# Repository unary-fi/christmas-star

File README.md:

# Christmas Star

A decorative smart LED Christmas star: 132 RGB LEDs on two faces, Bluetooth,
an accelerometer and a 2 Gbit flash for animations. This repository holds the
hardware design (KiCad), the Zephyr firmware, the Android app and the PC tools.

Releases (firmware images and the Android app) are published in
[unary-fi/christmas-star-releases](https://github.com/unary-fi/christmas-star-releases/releases).

# Hardware

The ChristmasStar 1.0 hardware comprises the following components:
- STM32F030RCT6 ARM Cortex-M0 MCU (256 KB flash, 32 KB RAM)
- 8.0 MHz oscillator
- BM78SPPS5MC2 BlueTooth serial port module
- LSM6DS3 iNEMO 6-axis MEMS inertial module
- ZD35Q2GC-IB NAND Flash memory, 2 Gb
- 132 digital RGB LEDs in one chain, 66 LEDs per side

See [docs/led-layout.md](docs/led-layout.md) for how the LEDs are arranged and
[docs/hw-schematic-review.md](docs/hw-schematic-review.md) for known hardware issues.

# Software

The firmware in [sw/](sw/) is a [Zephyr](https://zephyrproject.org) application
with its own board definition (`christmas_star`). The Android app in
[android/](android/) controls the star over Bluetooth LE.

## Features

- Real-time LED effects at 50 fps. The LED data is sent by SPI2 (transmit-only)
  with DMA from the app's own driver, so it is unaffected by interrupts.
- Christmas effects that run on the star itself: Golden Star, Liquid Gold
  (flows as the star is tilted), Snowfall, Shooting Stars, Candlelight,
  Hearth & Frost (different faces that trade places), Northern Lights, Candy
  Cane, Tree Lights, Star of Bethlehem, Fireworks, Christmas Disco, Frost, Twinkle, Comets and
  Rainbow, with an adjustable speed.
- The app and Star Studio get the effect list and animated previews from the
  star (`app effects`, `app preview`), so new effects arrive with a firmware
  update alone. Previews are cached per firmware version.
- Shake to drop: shaking knocks lights loose in their current colours, on top
  of any effect, picture or video (`shake on|off`).
- **Comet**, a game played on the star and steered from the app (see
  *Comet, the game*).
- Command line over Bluetooth (BM78), including direct LED control and a
  binary live-stream mode used by the app for photos and videos.
- One effect at a time in the 2 Gbit NAND (about 655 000 frames, 3.6 h at
  50 fps), uploaded over Bluetooth with XMODEM-1K.
- The star resumes what it was showing after a restart (effect, manual or
  picture frame, speed, shake on/off).
- Missing LEDs: if an LED is bridged on the board, or is faulty and only
  passes the data through, mark it missing and the firmware skips it in the
  chain. The default list is empty (`CONFIG_STAR_DEFAULT_MISSING_LEDS`); the
  first prototype has D259 bridged (`led missing add D259`).
- Supply protection: the firmware measures the 3V3 rail every frame and
  lowers the LED current limit when it sags, so the Bluetooth module (3.3 V
  minimum) keeps running. The default limit is 600 mA (`led limit`);
  `led status` shows the rail voltage and the learnt limit.
- Pairing: each star belongs to one phone (or PC). Its Bluetooth command line
  stays locked until the app proves the owner's key, so several stars and
  phones can share a room. A developer key opens every star (see *Pairing*).
- Names: stars can be renamed from the app or Star Studio; the name is what
  phones and PCs see when they search.
- Settings (missing LEDs, brightness, current limit, IMU axes) and the
  running state are stored in the MCU's internal flash.

## Setting up (Windows)

1. Install Python 3.12, CMake, Ninja and the SEGGER J-Link software.
2. Create the Python environment and the west workspace (the repository root
   is the workspace, `sw/` is the manifest):

   ```powershell
   py -3.12 -m venv .venv
   .venv\Scripts\pip install west pyserial xmodem pillow pylink-square pytest bleak cryptography intelhex click cbor2
   .venv\Scripts\west init -l sw
   .venv\Scripts\west update
   .venv\Scripts\pip install -r zephyr\scripts\requirements-base.txt
   ```

3. Install the [Zephyr SDK](https://github.com/zephyrproject-rtos/sdk-ng/releases)
   1.0.1 minimal bundle with the `arm-zephyr-eabi` toolchain into
   `%USERPROFILE%\zephyr-sdk-1.0.1`.
4. In each new PowerShell session: `. .\sw\tools\env.ps1`
5. Developer key (optional, for your own builds only): put 32 random hex
   digits in `sw/dev_key.txt` (ignored by git), e.g.
   `python -c "import secrets; open('sw/dev_key.txt','w').write(secrets.token_hex(16))"`.
   Firmware built with it accepts this key on every star; `star_ble.py` reads
   it from the same file, and Star Studio takes it on its *Developer* page.
   Keep it private, and never
   publish firmware built with it: anyone could read the key out of the image.
   Published releases are built without one (CI has no key; locally,
   `$env:STAR_NO_DEV_KEY = "1"` before a pristine build leaves it out).

## Building and flashing

```powershell
west build --sysbuild -b christmas_star sw -d build/star            # release
west build --sysbuild -b christmas_star sw -d build/debug -- -DEXTRA_CONF_FILE=debug.conf
west flash -d build/star                                 # J-Link on J401
```

Each build contains the MCUboot bootloader and the firmware, signed with
`sw/signing_key.pem` (ECDSA P-256, ignored by git). Stars only start firmware
signed with the key their bootloader was built with. Official releases are
signed with the project's key, which is not public; for your own builds,
create a key of your own and install your bootloader once with a J-Link:

```powershell
python bootloader\mcuboot\scripts\imgtool.py keygen -k sw\signing_key.pem -t ecdsa-p256
```

Flash layout (256 KB): MCUboot 32 KB, the running firmware 108 KB, the slot
for an update 108 KB, settings 8 KB (at the same place as before the
bootloader, so the stored settings survive). The version comes from
[sw/VERSION](sw/VERSION).

### Firmware update over Bluetooth

```powershell
python sw\tools\update_firmware.py build\star\sw\zephyr\zephyr.signed.bin
python sw\tools\update_firmware.py --star "Living room" build\star\sw\zephyr\zephyr.signed.bin
```

or the *Firmware* card in Star Studio (several stars, one after the other).
The image goes into the second slot with XMODEM-1K (about 35 s from a PC);
`fw apply` restarts the star and MCUboot checks the signature and swaps the
slots. The new firmware confirms itself after 20 s; if it crashes or hangs
before that, the next restart brings the old one back. On the command line:
`fw status`, `fw upload`, `fw apply [permanent]`, `fw confirm`.

Updates need the BOOT0 pull-down: without it, the restart ends in ST's ROM
bootloader. Boards are switched to the bootloader layout once with the
J-Link (`west flash`); after that, Bluetooth is enough.

The debug build adds a second shell over SEGGER RTT, so the star can be
controlled through the J-Link without Bluetooth:

```powershell
python sw\tools\rtt_shell.py --boot-flash "led status" "nand info" "imu read"
```

The debug build can also reach the BM78 through the J-Link: `bt bridge test`
restarts the module in test mode and relays its UART over RTT.
`python sw\tools\bm78_bridge.py probe|dump|hci|com|rename|restore` uses this
to read the module's version and configuration EEPROM, rename the module,
write a backup back (keep backups private: they contain the module's address and
pairing keys), or connect Microchip's
configuration tool through a virtual null-modem pair (com0com).

> **BOOT0 on hardware 1.0:** BOOT0 has no pull-down, and on the prototype
> every reset starts ST's ROM bootloader instead of the firmware. Connecting
> the J-Link also resets the MCU. Until the board gets a 10 kΩ pull-down,
> start the firmware with `rtt_shell.py --boot-flash`, which maps flash to
> address 0 and starts MCUboot, which starts the firmware.

## Tests

```powershell
west build -p always -b qemu_cortex_m3 sw/tests/unit -d build/tests -t run
python -m pytest sw/tools/tests pc/tests
```

## Command line

The star's Bluetooth module appears under its name (**"Dual-SPP"** until it is
first renamed; after renaming it is also found by its service, whatever the
name). Windows 11's
*Add device* dialog may not list it; pair it with the classic wizard instead
(run `DevicePairingWizard.exe`). Windows pairs it as a Bluetooth LE device,
which creates no COM port, so use the BLE terminal:

```powershell
python sw\tools\star_ble.py --list             # nearby stars
python sw\tools\star_ble.py                    # interactive terminal (nearest star)
python sw\tools\star_ble.py --star "Living room" "led status"
python sw\tools\star_ble.py --pair             # pair the star with this PC
```

The tool logs in with the developer key, or with this PC's own key
(`~/.christmas-star/pc_key`) for a star paired with the PC.

Phones can use any BLE terminal app that supports the Microchip Transparent
UART service. On a system where the star pairs as a Classic SPP device, open
its COM port at 115200 baud instead. Type `help` for all commands.

| Command | Description |
|---|---|
| `set_led <side> <index> <color>` | Set one LED. Side 0 = both, 1 = front (D2xx), 2 = back (D3xx); index 1–66 is the designator number; colour `0xRRGGBB`, `#RRGGBB` or `RRGGBB`. Example: `set_led 1 32 0xffee33` sets D232. |
| `set_all <side> <color>` | Set all LEDs of a side, e.g. `set_all 1 0xffee33`. |
| `effect list` | Effects, and the one stored in the flash. |
| `effect play <name\|flash>` | Start an effect (`flash` = the stored one). |
| `effect color <color>` | Solid colour. |
| `effect speed [25-400]` | Effect speed in percent. |
| `effect upload` | Receive a `.csfx` file with XMODEM-1K (replaces the stored effect). |
| `effect info`, `effect delete` | Stored effect details, delete it. |
| `shake [on\|off]` | Shake to drop lights, for every effect. |
| `app hello`, `app state`, `stream` | Used by the Android app (state line, binary live frames). |
| `app effects`, `app preview <id> [frames] [step_ms]` | The effects to offer (`fx <id> <flags> <title>\|<subtitle>`), and a preview clip rendered on the star. |
| `app game [start single\|double \| l \| r \| f \| pause \| resume \| stop]` | Comet, the game: start, steer (left, right, flip), pause, leave. Without arguments one `game state=... score=... best1=... best2=...` line. |
| `led missing list\|add\|del\|clear` | LEDs bridged on the board, e.g. `led missing add D259`. |
| `led test <led\|all>` | Light one LED (e.g. `D232` or logical index 0–131) or walk the chain. |
| `led brightness [0-255]`, `led limit [mA]` | Global brightness, total current limit. |
| `led map [1\|2]`, `led status` | Print the LED bitmap; frame rate and current. |
| `imu read [n]`, `imu axis [+x+y+z]`, `imu threshold [mg]` | Accelerometer values, axis mapping, shake sensitivity. |
| `bt status`, `bt reset` | Bluetooth module status pins, reset. |
| `star name [text\|--default]` | Show or set the star's name (1–16 characters, what phones see). Bluetooth restarts for a few seconds. |
| `star unpair [force]` | Release the star from its owner (`force` with developer access). |
| `star pairing [open\|reset]` | Pairing status; open the window or forget the owner (developer or J-Link). |
| `app hello`, `app auth <hmac>`, `app pair <key>` | Unlock the Bluetooth command line (see *Pairing*). |
| `nand info`, `nand test <block>` | Flash ID and geometry, read/write test. |
| `reboot` | Restart. |

## Pairing

Every star has at most one owner: a phone (the app) or a PC. Until a client
proves a key, the star's Bluetooth command line only answers `app hello`,
`app auth` and `app pair`, and it locks again whenever the link drops. The
J-Link (RTT) command line is never locked.

- `app hello` gives a fresh random nonce; the client answers
  `app auth <HMAC-SHA256(key, "auth" + nonce)>` with the owner's key or the
  developer key. The key itself never goes over the air.
- A star without an owner (new, or released by its owner) accepts a new owner
  during the first **60 s after it is plugged in**. An owned star does not.
- **Shaking the star for 5 seconds** opens pairing in any case: the star
  breathes gold for 60 s, and the next phone that taps it in the app becomes
  its owner (green flash). Releasing shows a red flash.
- The owner can release the star in the app (*Stars* → *Release this star*).
- Developer mode in the app: tap the title "Christmas Star" seven times and
  enter the developer key; *Stars* then switches freely between all stars.
  Star Studio uses the developer key saved on its *Developer* page.

The BM78 accepts one connection at a time, so a star connected to Star Studio
is not available to a phone until the studio disconnects it.

## Comet, the game

A comet runs along the star's lights. Catch the golden sparks to grow (and
the red ornaments for five points); don't run into your own tail. Every five
sparks the comet speeds up; at 40 segments the star is full and you win.

- **The track**: on each face the outline and the inner circle (the 12 LEDs
  around the centre), joined by six passages: the single LEDs between them,
  each leading from an inner corner of the outline to the circle.
- **Steering**: the comet follows its line. Tap *Left* or *Right* and it turns
  that way at the next place where it can, if that turn exists there;
  otherwise the tap is forgotten. At the end of a passage the comet turns to
  the side you tapped last (before your first tap, it keeps its direction of
  travel). A faint white light shows the next place to turn; it turns blue
  when your tap will take it. Left and right are as you see them on the face
  the comet is on.
- **One side**: the game stays on the front and is mirrored to the back, so
  everyone around the star sees the same game.
- **Both sides**: *Flip* sends the comet through the star; it carries on in
  the same direction on the other face. Sparks appear on either face, so walk
  around the star to find them, and mind your tail when you flip onto it.
  Sparks count double. A faint glow on the far face shows where the comet is.
- The app and Star Studio have a *Play* page (firmware 1.6 or later). In Star
  Studio, steer with the arrow keys (or A/D, W/S to flip), Space pauses and
  Esc leaves; every selected star plays. Leaving the app or losing the
  Bluetooth link pauses the game; after a minute in pause or game over the
  star goes back to the effect it showed before. Each mode keeps its best
  score on the star.

The rules are in `sw/src/game/comet_logic.c` (unit-tested), the drawing in
`fx_cometgame.c`.

# Star Studio (PC)

Star Studio controls every star in the room from a computer, with the app's
look. It is a web page that talks to the stars itself, with Web Bluetooth:
nothing to install.

**Open https://unary-fi.github.io/christmas-star/ in Chrome or Edge** (Windows,
macOS, ChromeOS, Android; on Linux, Chrome may need
`chrome://flags/#enable-web-bluetooth`). Firefox and Safari have no Web
Bluetooth.

- Left: your stars. *Add star* opens the browser's Bluetooth chooser; pick a
  star and it connects. Where the browser remembers permissions, the stars
  come back on the next visit. Click to select; Ctrl+click selects several
  stars, which then all get the same commands, colours, pictures and effects.
- Stars open with the developer key (*Developer* page, kept in this browser
  only) or with this browser's own key: a star in its pairing window (shake
  it for 5 s) pairs with *Pair*, like a phone.
- *Colour*, *Picture* (photo or video, live or saved to the star) and
  *Effects* work as in the app.
- *Developer*: a console for every selected star, status and supply, renaming
  (several stars at once get numbered names), pairing, missing LEDs (click an
  LED on the star), the current limit and `.csfx` uploads.

The page is `pc/web` (plain HTML, CSS and JavaScript modules, no build step
and no libraries), published by `.github/workflows/pages.yml`. To work on it,
serve it locally (`localhost` counts as secure for Web Bluetooth) and run its
tests with Node.js:

```powershell
cd pc\web
python -m http.server 8000      # then open http://localhost:8000
node --test
```

## Making effects

Draw a 32×32 image or animated GIF using the bitmap in
[docs/led-layout.md](docs/led-layout.md) as a template, then:

```powershell
python sw\tools\make_effect.py snow.gif -o snow.csfx --loop
python sw\tools\send_effect.py --ble snow.csfx --play       # Bluetooth LE
python sw\tools\send_effect.py --port COM12 snow.csfx        # serial port
```

Over BLE, uploads run at about 2.3 KB/s from Windows and 4.6 KB/s from the
Android app (one second of 50 fps animation is about 20 KB). With a serial
port, Tera Term's *File → Transfer → XMODEM → Send* (1K) also works after
typing `effect upload`.

# Android app

The app ([android/](android/), Kotlin + Jetpack Compose, Android 9 or newer)
finds the star ("Dual-SPP") over Bluetooth LE and has three pages:

- **Colour:** red, green and blue sliders for the front, the back or both
  faces (choosing *Both* copies the front colour to the back), plus festive
  presets.
- **Picture:** choose a photo or video and move or zoom it behind the star's
  outline. The star shows the colours under its LEDs live (about 20 frames/s),
  the same picture on both faces. A photo stays on the star when you leave the
  page. A video loop can be saved into the star's flash and keeps playing
  without the app.
- **Effects:** animated previews of the star's Christmas effects; tap one to
  play it on the star. A speed slider sits on top.

The top bar shows the connected star and has the brightness slider and the
*Shake to drop* switch. Tap the star's name to open *Stars*: the stars nearby,
pairing, renaming and releasing (see *Pairing*). All effects run on the star itself, so everything
keeps going when the phone disconnects.

## Building the app

Requires JDK 17 and the Android SDK (platform 37). From `android/`:

```powershell
$env:JAVA_HOME = "C:\Program Files\Microsoft\jdk-17.0.21.21-hotspot"
.\gradlew.bat assembleDebug testDebugUnitTest lintDebug
adb install -r app\build\outputs\apk\debug\app-debug.apk
```

Release builds for Google Play (application ID `fi.unary.christmasstar`,
signed with the upload key in the git-ignored `android/keystore.properties`):
see [android/play/RELEASE.md](android/play/RELEASE.md). The store texts,
graphics and privacy policy are in [android/play/](android/play/).

The star outline and LED positions in the app come from the PCB files:
`sw/tools/gen_led_layout.py` regenerates `StarLayout.kt` together with the
firmware's layout table.

# Contributing

Issues and pull requests are welcome. The `main` branch, merges and releases
are maintained by the project owners; to contribute, fork the repository,
make your change on a branch and open a pull request. Every pull request runs
the CI (firmware builds and unit tests, Android build, tests and lint, Python
tests); a maintainer approves the first run from a new contributor. See
[CONTRIBUTING.md](CONTRIBUTING.md).

# License

- Software (firmware, Android app, PC tools): [MIT](LICENSE)
- Hardware design files in [hw/](hw/): [CERN-OHL-P-2.0](hw/LICENSE)

Copyright (c) 2024-2026 Tuomas Terho.

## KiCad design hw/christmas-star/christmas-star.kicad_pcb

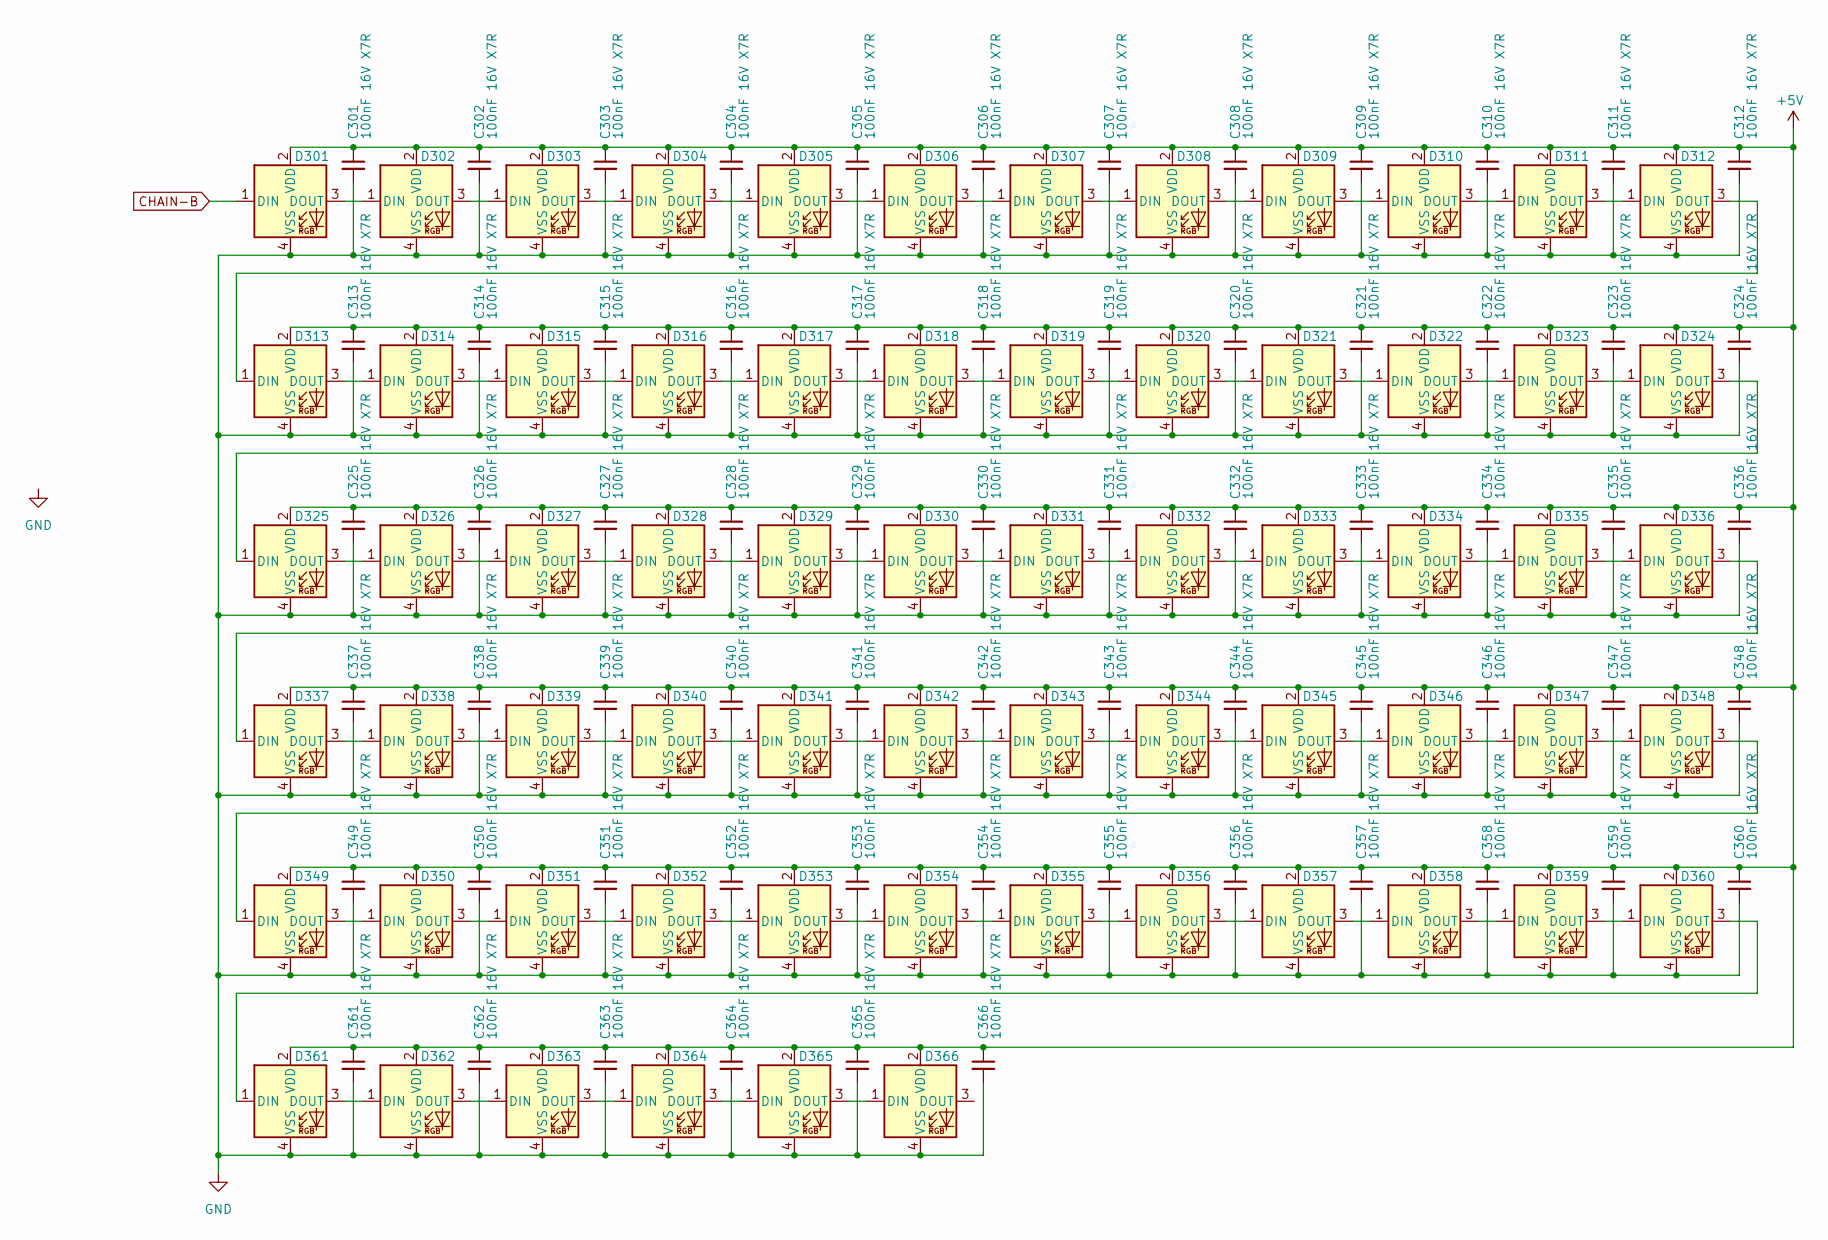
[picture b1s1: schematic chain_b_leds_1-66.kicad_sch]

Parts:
C301, C302, C303, C304, C305, C306, C307, C308, C309, C310, C311, C312, C313, C314, C315, C316, C317, C318, C319, C320, C321, C322, C323, C324, C325, C326, C327, C328, C329, C330, C331, C332, C333, C334, C335, C336, C337, C338, C339, C340, C341, C342, C343, C344, C345, C346, C347, C348, C349, C350, C351, C352, C353, C354, C355, C356, C357, C358, C359, C360, C361, C362, C363, C364, C365, C366: 100nF 16V X7R; C_0402_1005Metric; JLCPCB Part # C328914
D301, D302, D303, D304, D305, D306, D307, D308, D309, D310, D311, D312, D313, D314, D315, D316, D317, D318, D319, D320, D321, D322, D323, D324, D325, D326, D327, D328, D329, D330, D331, D332, D333, D334, D335, D336, D337, D338, D339, D340, D341, D342, D343, D344, D345, D346, D347, D348, D349, D350, D351, D352, D353, D354, D355, D356, D357, D358, D359, D360, D361, D362, D363, D364, D365, D366: DY-S1515065/RGBC/6805-5T; LED_0606; JLCPCB Part # C524053

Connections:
+5V: C301.1, C302.1, C303.1, C304.1, C305.1, C306.1, C307.1, C308.1, C309.1, C310.1, C311.1, C312.1, C313.1, C314.1, C315.1, C316.1, C317.1, C318.1, C319.1, C320.1, C321.1, C322.1, C323.1, C324.1, C325.1, C326.1, C327.1, C328.1, C329.1, C330.1, C331.1, C332.1, C333.1, C334.1, C335.1, C336.1, C337.1, C338.1, C339.1, C340.1, C341.1, C342.1, C343.1, C344.1, C345.1, C346.1, C347.1, C348.1, C349.1, C350.1, C351.1, C352.1, C353.1, C354.1, C355.1, C356.1, C357.1, C358.1, C359.1, C360.1, C361.1, C362.1, C363.1, C364.1, C365.1, C366.1, D301.2 (VDD), D302.2 (VDD), D303.2 (VDD), D304.2 (VDD), D305.2 (VDD), D306.2 (VDD), D307.2 (VDD), D308.2 (VDD), D309.2 (VDD), D310.2 (VDD), D311.2 (VDD), D312.2 (VDD), D313.2 (VDD), D314.2 (VDD), D315.2 (VDD), D316.2 (VDD), D317.2 (VDD), D318.2 (VDD), D319.2 (VDD), D320.2 (VDD), D321.2 (VDD), D322.2 (VDD), D323.2 (VDD), D324.2 (VDD), D325.2 (VDD), D326.2 (VDD), D327.2 (VDD), D328.2 (VDD), D329.2 (VDD), D330.2 (VDD), D331.2 (VDD), D332.2 (VDD), D333.2 (VDD), D334.2 (VDD), D335.2 (VDD), D336.2 (VDD), D337.2 (VDD), D338.2 (VDD), D339.2 (VDD), D340.2 (VDD), D341.2 (VDD), D342.2 (VDD), D343.2 (VDD), D344.2 (VDD), D345.2 (VDD), D346.2 (VDD), D347.2 (VDD), D348.2 (VDD), D349.2 (VDD), D350.2 (VDD), D351.2 (VDD), D352.2 (VDD), D353.2 (VDD), D354.2 (VDD), D355.2 (VDD), D356.2 (VDD), D357.2 (VDD), D358.2 (VDD), D359.2 (VDD), D360.2 (VDD), D361.2 (VDD), D362.2 (VDD), D363.2 (VDD), D364.2 (VDD), D365.2 (VDD), D366.2 (VDD); also elsewhere on the board
CHAIN-B: D301.1 (DIN); also elsewhere on the board
GND: C301.2, C302.2, C303.2, C304.2, C305.2, C306.2, C307.2, C308.2, C309.2, C310.2, C311.2, C312.2, C313.2, C314.2, C315.2, C316.2, C317.2, C318.2, C319.2, C320.2, C321.2, C322.2, C323.2, C324.2, C325.2, C326.2, C327.2, C328.2, C329.2, C330.2, C331.2, C332.2, C333.2, C334.2, C335.2, C336.2, C337.2, C338.2, C339.2, C340.2, C341.2, C342.2, C343.2, C344.2, C345.2, C346.2, C347.2, C348.2, C349.2, C350.2, C351.2, C352.2, C353.2, C354.2, C355.2, C356.2, C357.2, C358.2, C359.2, C360.2, C361.2, C362.2, C363.2, C364.2, C365.2, C366.2, D301.4 (VSS), D302.4 (VSS), D303.4 (VSS), D304.4 (VSS), D305.4 (VSS), D306.4 (VSS), D307.4 (VSS), D308.4 (VSS), D309.4 (VSS), D310.4 (VSS), D311.4 (VSS), D312.4 (VSS), D313.4 (VSS), D314.4 (VSS), D315.4 (VSS), D316.4 (VSS), D317.4 (VSS), D318.4 (VSS), D319.4 (VSS), D320.4 (VSS), D321.4 (VSS), D322.4 (VSS), D323.4 (VSS), D324.4 (VSS), D325.4 (VSS), D326.4 (VSS), D327.4 (VSS), D328.4 (VSS), D329.4 (VSS), D330.4 (VSS), D331.4 (VSS), D332.4 (VSS), D333.4 (VSS), D334.4 (VSS), D335.4 (VSS), D336.4 (VSS), D337.4 (VSS), D338.4 (VSS), D339.4 (VSS), D340.4 (VSS), D341.4 (VSS), D342.4 (VSS), D343.4 (VSS), D344.4 (VSS), D345.4 (VSS), D346.4 (VSS), D347.4 (VSS), D348.4 (VSS), D349.4 (VSS), D350.4 (VSS), D351.4 (VSS), D352.4 (VSS), D353.4 (VSS), D354.4 (VSS), D355.4 (VSS), D356.4 (VSS), D357.4 (VSS), D358.4 (VSS), D359.4 (VSS), D360.4 (VSS), D361.4 (VSS), D362.4 (VSS), D363.4 (VSS), D364.4 (VSS), D365.4 (VSS), D366.4 (VSS); also elsewhere on the board
unnamed: D301.3 (DOUT), D302.1 (DIN)
unnamed: D302.3 (DOUT), D303.1 (DIN)
unnamed: D303.3 (DOUT), D304.1 (DIN)
unnamed: D304.3 (DOUT), D305.1 (DIN)
unnamed: D305.3 (DOUT), D306.1 (DIN)
unnamed: D306.3 (DOUT), D307.1 (DIN)
unnamed: D307.3 (DOUT), D308.1 (DIN)
unnamed: D308.3 (DOUT), D309.1 (DIN)
unnamed: D309.3 (DOUT), D310.1 (DIN)
unnamed: D310.3 (DOUT), D311.1 (DIN)
unnamed: D311.3 (DOUT), D312.1 (DIN)
unnamed: D312.3 (DOUT), D313.1 (DIN)
unnamed: D313.3 (DOUT), D314.1 (DIN)
unnamed: D314.3 (DOUT), D315.1 (DIN)
unnamed: D315.3 (DOUT), D316.1 (DIN)
unnamed: D316.3 (DOUT), D317.1 (DIN)
unnamed: D317.3 (DOUT), D318.1 (DIN)
unnamed: D318.3 (DOUT), D319.1 (DIN)
unnamed: D319.3 (DOUT), D320.1 (DIN)
unnamed: D320.3 (DOUT), D321.1 (DIN)
unnamed: D321.3 (DOUT), D322.1 (DIN)
unnamed: D322.3 (DOUT), D323.1 (DIN)
unnamed: D323.3 (DOUT), D324.1 (DIN)
unnamed: D324.3 (DOUT), D325.1 (DIN)
unnamed: D325.3 (DOUT), D326.1 (DIN)
unnamed: D326.3 (DOUT), D327.1 (DIN)
unnamed: D327.3 (DOUT), D328.1 (DIN)
unnamed: D328.3 (DOUT), D329.1 (DIN)
unnamed: D329.3 (DOUT), D330.1 (DIN)
unnamed: D330.3 (DOUT), D331.1 (DIN)
unnamed: D331.3 (DOUT), D332.1 (DIN)
unnamed: D332.3 (DOUT), D333.1 (DIN)
unnamed: D333.3 (DOUT), D334.1 (DIN)
unnamed: D334.3 (DOUT), D335.1 (DIN)
unnamed: D335.3 (DOUT), D336.1 (DIN)
unnamed: D336.3 (DOUT), D337.1 (DIN)
unnamed: D337.3 (DOUT), D338.1 (DIN)
unnamed: D338.3 (DOUT), D339.1 (DIN)
unnamed: D339.3 (DOUT), D340.1 (DIN)
unnamed: D340.3 (DOUT), D341.1 (DIN)
unnamed: D341.3 (DOUT), D342.1 (DIN)
unnamed: D342.3 (DOUT), D343.1 (DIN)
unnamed: D343.3 (DOUT), D344.1 (DIN)
unnamed: D344.3 (DOUT), D345.1 (DIN)
unnamed: D345.3 (DOUT), D346.1 (DIN)
unnamed: D346.3 (DOUT), D347.1 (DIN)
unnamed: D347.3 (DOUT), D348.1 (DIN)
unnamed: D348.3 (DOUT), D349.1 (DIN)
unnamed: D349.3 (DOUT), D350.1 (DIN)
unnamed: D350.3 (DOUT), D351.1 (DIN)
unnamed: D351.3 (DOUT), D352.1 (DIN)
unnamed: D352.3 (DOUT), D353.1 (DIN)
unnamed: D353.3 (DOUT), D354.1 (DIN)
unnamed: D354.3 (DOUT), D355.1 (DIN)
unnamed: D355.3 (DOUT), D356.1 (DIN)
unnamed: D356.3 (DOUT), D357.1 (DIN)
unnamed: D357.3 (DOUT), D358.1 (DIN)
unnamed: D358.3 (DOUT), D359.1 (DIN)
unnamed: D359.3 (DOUT), D360.1 (DIN)
unnamed: D360.3 (DOUT), D361.1 (DIN)
unnamed: D361.3 (DOUT), D362.1 (DIN)
unnamed: D362.3 (DOUT), D363.1 (DIN)
unnamed: D363.3 (DOUT), D364.1 (DIN)
unnamed: D364.3 (DOUT), D365.1 (DIN)
unnamed: D365.3 (DOUT), D366.1 (DIN)

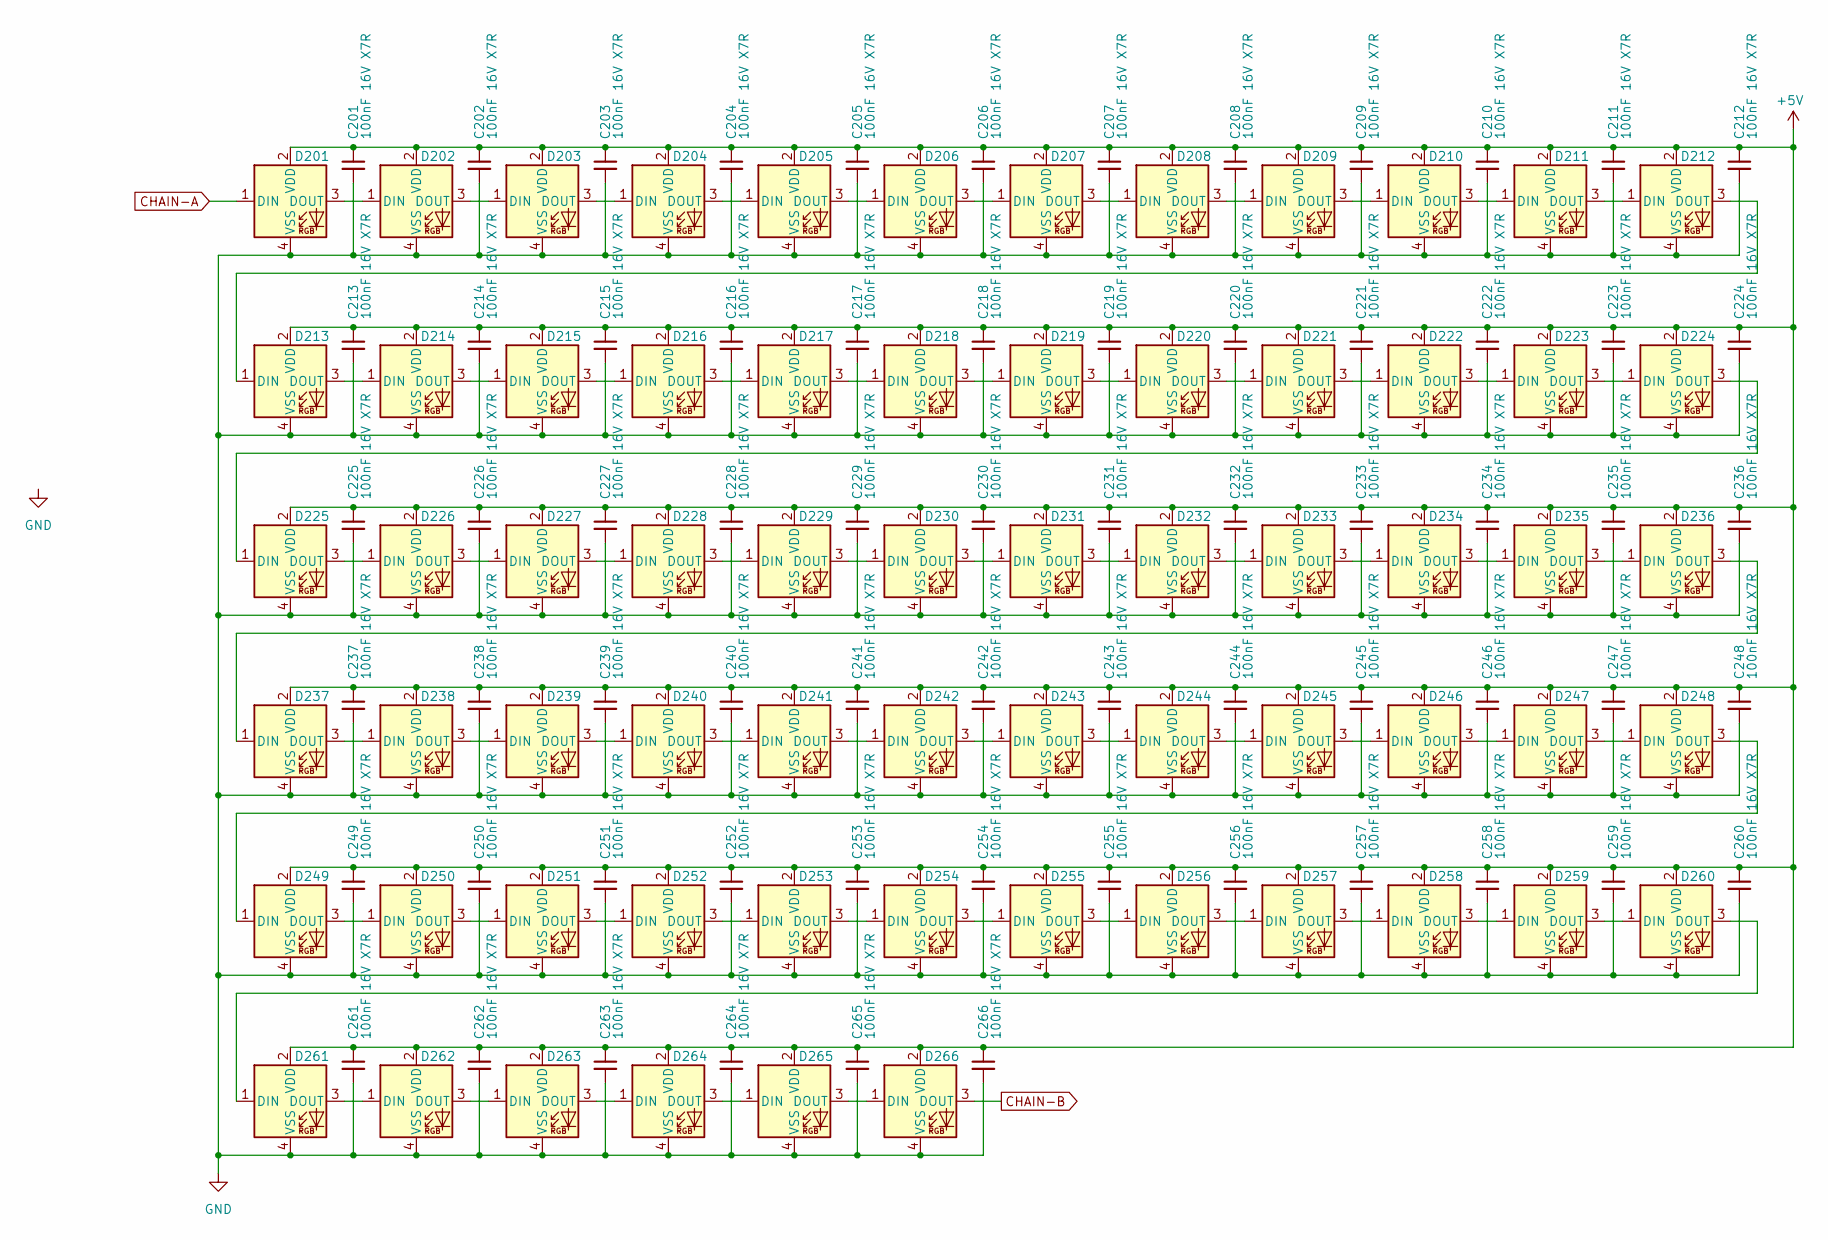
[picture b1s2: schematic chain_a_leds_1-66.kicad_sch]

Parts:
C201, C202, C203, C204, C205, C206, C207, C208, C209, C210, C211, C212, C213, C214, C215, C216, C217, C218, C219, C220, C221, C222, C223, C224, C225, C226, C227, C228, C229, C230, C231, C232, C233, C234, C235, C236, C237, C238, C239, C240, C241, C242, C243, C244, C245, C246, C247, C248, C249, C250, C251, C252, C253, C254, C255, C256, C257, C258, C259, C260, C261, C262, C263, C264, C265, C266: 100nF 16V X7R; C_0402_1005Metric; JLCPCB Part # C328914
D201, D202, D203, D204, D205, D206, D207, D208, D209, D210, D211, D212, D213, D214, D215, D216, D217, D218, D219, D220, D221, D222, D223, D224, D225, D226, D227, D228, D229, D230, D231, D232, D233, D234, D235, D236, D237, D238, D239, D240, D241, D242, D243, D244, D245, D246, D247, D248, D249, D250, D251, D252, D253, D254, D255, D256, D257, D258, D259, D260, D261, D262, D263, D264, D265, D266: DY-S1515065/RGBC/6805-5T; LED_0606; JLCPCB Part # C524053

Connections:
+5V: C201.1, C202.1, C203.1, C204.1, C205.1, C206.1, C207.1, C208.1, C209.1, C210.1, C211.1, C212.1, C213.1, C214.1, C215.1, C216.1, C217.1, C218.1, C219.1, C220.1, C221.1, C222.1, C223.1, C224.1, C225.1, C226.1, C227.1, C228.1, C229.1, C230.1, C231.1, C232.1, C233.1, C234.1, C235.1, C236.1, C237.1, C238.1, C239.1, C240.1, C241.1, C242.1, C243.1, C244.1, C245.1, C246.1, C247.1, C248.1, C249.1, C250.1, C251.1, C252.1, C253.1, C254.1, C255.1, C256.1, C257.1, C258.1, C259.1, C260.1, C261.1, C262.1, C263.1, C264.1, C265.1, C266.1, D201.2 (VDD), D202.2 (VDD), D203.2 (VDD), D204.2 (VDD), D205.2 (VDD), D206.2 (VDD), D207.2 (VDD), D208.2 (VDD), D209.2 (VDD), D210.2 (VDD), D211.2 (VDD), D212.2 (VDD), D213.2 (VDD), D214.2 (VDD), D215.2 (VDD), D216.2 (VDD), D217.2 (VDD), D218.2 (VDD), D219.2 (VDD), D220.2 (VDD), D221.2 (VDD), D222.2 (VDD), D223.2 (VDD), D224.2 (VDD), D225.2 (VDD), D226.2 (VDD), D227.2 (VDD), D228.2 (VDD), D229.2 (VDD), D230.2 (VDD), D231.2 (VDD), D232.2 (VDD), D233.2 (VDD), D234.2 (VDD), D235.2 (VDD), D236.2 (VDD), D237.2 (VDD), D238.2 (VDD), D239.2 (VDD), D240.2 (VDD), D241.2 (VDD), D242.2 (VDD), D243.2 (VDD), D244.2 (VDD), D245.2 (VDD), D246.2 (VDD), D247.2 (VDD), D248.2 (VDD), D249.2 (VDD), D250.2 (VDD), D251.2 (VDD), D252.2 (VDD), D253.2 (VDD), D254.2 (VDD), D255.2 (VDD), D256.2 (VDD), D257.2 (VDD), D258.2 (VDD), D259.2 (VDD), D260.2 (VDD), D261.2 (VDD), D262.2 (VDD), D263.2 (VDD), D264.2 (VDD), D265.2 (VDD), D266.2 (VDD); also elsewhere on the board
CHAIN-A: D201.1 (DIN); also elsewhere on the board
CHAIN-B: D266.3 (DOUT); also elsewhere on the board
GND: C201.2, C202.2, C203.2, C204.2, C205.2, C206.2, C207.2, C208.2, C209.2, C210.2, C211.2, C212.2, C213.2, C214.2, C215.2, C216.2, C217.2, C218.2, C219.2, C220.2, C221.2, C222.2, C223.2, C224.2, C225.2, C226.2, C227.2, C228.2, C229.2, C230.2, C231.2, C232.2, C233.2, C234.2, C235.2, C236.2, C237.2, C238.2, C239.2, C240.2, C241.2, C242.2, C243.2, C244.2, C245.2, C246.2, C247.2, C248.2, C249.2, C250.2, C251.2, C252.2, C253.2, C254.2, C255.2, C256.2, C257.2, C258.2, C259.2, C260.2, C261.2, C262.2, C263.2, C264.2, C265.2, C266.2, D201.4 (VSS), D202.4 (VSS), D203.4 (VSS), D204.4 (VSS), D205.4 (VSS), D206.4 (VSS), D207.4 (VSS), D208.4 (VSS), D209.4 (VSS), D210.4 (VSS), D211.4 (VSS), D212.4 (VSS), D213.4 (VSS), D214.4 (VSS), D215.4 (VSS), D216.4 (VSS), D217.4 (VSS), D218.4 (VSS), D219.4 (VSS), D220.4 (VSS), D221.4 (VSS), D222.4 (VSS), D223.4 (VSS), D224.4 (VSS), D225.4 (VSS), D226.4 (VSS), D227.4 (VSS), D228.4 (VSS), D229.4 (VSS), D230.4 (VSS), D231.4 (VSS), D232.4 (VSS), D233.4 (VSS), D234.4 (VSS), D235.4 (VSS), D236.4 (VSS), D237.4 (VSS), D238.4 (VSS), D239.4 (VSS), D240.4 (VSS), D241.4 (VSS), D242.4 (VSS), D243.4 (VSS), D244.4 (VSS), D245.4 (VSS), D246.4 (VSS), D247.4 (VSS), D248.4 (VSS), D249.4 (VSS), D250.4 (VSS), D251.4 (VSS), D252.4 (VSS), D253.4 (VSS), D254.4 (VSS), D255.4 (VSS), D256.4 (VSS), D257.4 (VSS), D258.4 (VSS), D259.4 (VSS), D260.4 (VSS), D261.4 (VSS), D262.4 (VSS), D263.4 (VSS), D264.4 (VSS), D265.4 (VSS), D266.4 (VSS); also elsewhere on the board
unnamed: D201.3 (DOUT), D202.1 (DIN)
unnamed: D202.3 (DOUT), D203.1 (DIN)
unnamed: D203.3 (DOUT), D204.1 (DIN)
unnamed: D204.3 (DOUT), D205.1 (DIN)
unnamed: D205.3 (DOUT), D206.1 (DIN)
unnamed: D206.3 (DOUT), D207.1 (DIN)
unnamed: D207.3 (DOUT), D208.1 (DIN)
unnamed: D208.3 (DOUT), D209.1 (DIN)
unnamed: D209.3 (DOUT), D210.1 (DIN)
unnamed: D210.3 (DOUT), D211.1 (DIN)
unnamed: D211.3 (DOUT), D212.1 (DIN)
unnamed: D212.3 (DOUT), D213.1 (DIN)
unnamed: D213.3 (DOUT), D214.1 (DIN)
unnamed: D214.3 (DOUT), D215.1 (DIN)
unnamed: D215.3 (DOUT), D216.1 (DIN)
unnamed: D216.3 (DOUT), D217.1 (DIN)
unnamed: D217.3 (DOUT), D218.1 (DIN)
unnamed: D218.3 (DOUT), D219.1 (DIN)
unnamed: D219.3 (DOUT), D220.1 (DIN)
unnamed: D220.3 (DOUT), D221.1 (DIN)
unnamed: D221.3 (DOUT), D222.1 (DIN)
unnamed: D222.3 (DOUT), D223.1 (DIN)
unnamed: D223.3 (DOUT), D224.1 (DIN)
unnamed: D224.3 (DOUT), D225.1 (DIN)
unnamed: D225.3 (DOUT), D226.1 (DIN)
unnamed: D226.3 (DOUT), D227.1 (DIN)
unnamed: D227.3 (DOUT), D228.1 (DIN)
unnamed: D228.3 (DOUT), D229.1 (DIN)
unnamed: D229.3 (DOUT), D230.1 (DIN)
unnamed: D230.3 (DOUT), D231.1 (DIN)
unnamed: D231.3 (DOUT), D232.1 (DIN)
unnamed: D232.3 (DOUT), D233.1 (DIN)
unnamed: D233.3 (DOUT), D234.1 (DIN)
unnamed: D234.3 (DOUT), D235.1 (DIN)
unnamed: D235.3 (DOUT), D236.1 (DIN)
unnamed: D236.3 (DOUT), D237.1 (DIN)
unnamed: D237.3 (DOUT), D238.1 (DIN)
unnamed: D238.3 (DOUT), D239.1 (DIN)
unnamed: D239.3 (DOUT), D240.1 (DIN)
unnamed: D240.3 (DOUT), D241.1 (DIN)
unnamed: D241.3 (DOUT), D242.1 (DIN)
unnamed: D242.3 (DOUT), D243.1 (DIN)
unnamed: D243.3 (DOUT), D244.1 (DIN)
unnamed: D244.3 (DOUT), D245.1 (DIN)
unnamed: D245.3 (DOUT), D246.1 (DIN)
unnamed: D246.3 (DOUT), D247.1 (DIN)
unnamed: D247.3 (DOUT), D248.1 (DIN)
unnamed: D248.3 (DOUT), D249.1 (DIN)
unnamed: D249.3 (DOUT), D250.1 (DIN)
unnamed: D250.3 (DOUT), D251.1 (DIN)
unnamed: D251.3 (DOUT), D252.1 (DIN)
unnamed: D252.3 (DOUT), D253.1 (DIN)
unnamed: D253.3 (DOUT), D254.1 (DIN)
unnamed: D254.3 (DOUT), D255.1 (DIN)
unnamed: D255.3 (DOUT), D256.1 (DIN)
unnamed: D256.3 (DOUT), D257.1 (DIN)
unnamed: D257.3 (DOUT), D258.1 (DIN)
unnamed: D258.3 (DOUT), D259.1 (DIN)
unnamed: D259.3 (DOUT), D260.1 (DIN)
unnamed: D260.3 (DOUT), D261.1 (DIN)
unnamed: D261.3 (DOUT), D262.1 (DIN)
unnamed: D262.3 (DOUT), D263.1 (DIN)
unnamed: D263.3 (DOUT), D264.1 (DIN)
unnamed: D264.3 (DOUT), D265.1 (DIN)
unnamed: D265.3 (DOUT), D266.1 (DIN)

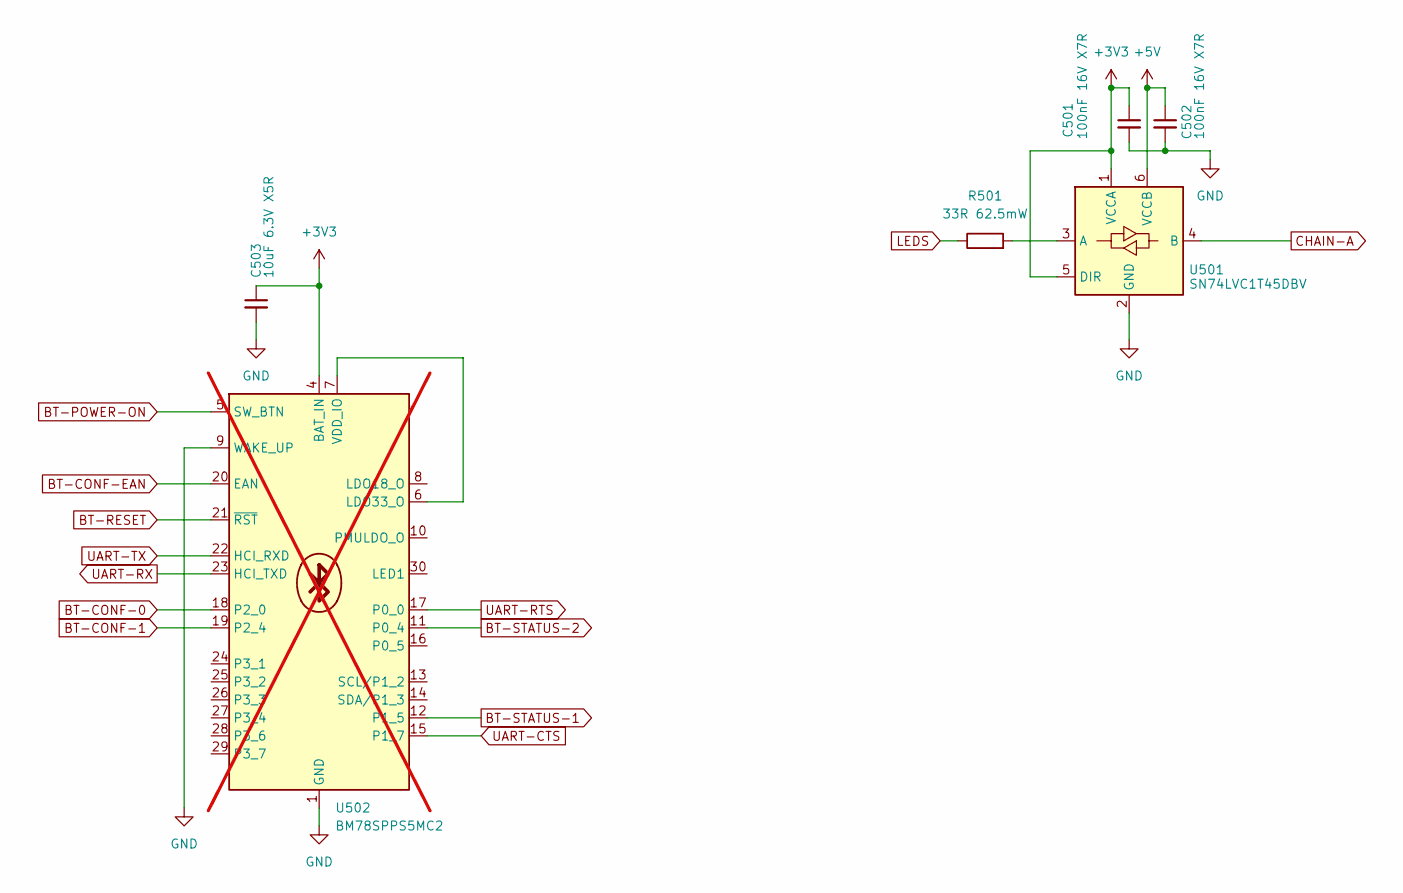
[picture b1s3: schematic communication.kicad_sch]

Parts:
C501, C502: 100nF 16V X7R; C_0402_1005Metric; JLCPCB Part # C328914
C503: 10uF 6.3V X5R; C_0402_1005Metric; JLCPCB Part # C15525
R501: 33R 62.5mW; R_0402_1005Metric; JLCPCB Part # C453643
U501: SN74LVC1T45DBV; SOT-363_SC-70-6; JLCPCB Part # C9382
U502: BM78SPPS5MC2; BM78SPPS5xC2; JLCPCB Part # C1526209; not fitted

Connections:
+3V3: C501.1, C503.1, U501.1 (VCCA), U501.5 (DIR), U502.4 (BAT_IN); also elsewhere on the board
+5V: C502.1, U501.6 (VCCB); also elsewhere on the board
BT-CONF-0: U502.18 (P2_0); also elsewhere on the board
BT-CONF-1: U502.19 (P2_4); also elsewhere on the board
BT-CONF-EAN: U502.20 (EAN); also elsewhere on the board
BT-POWER-ON: U502.5 (SW_BTN); also elsewhere on the board
BT-RESET: U502.21 (~RST); also elsewhere on the board
BT-STATUS-1: U502.12 (P1_5); also elsewhere on the board
BT-STATUS-2: U502.11 (P0_4); also elsewhere on the board
CHAIN-A: U501.4 (B); also elsewhere on the board
GND: C501.2, C502.2, C503.2, U501.2 (GND), U502.1 (GND), U502.2 (GND), U502.3 (GND), U502.9 (WAKE_UP), U502.31 (GND), U502.32 (GND), U502.33 (GND); also elsewhere on the board
LEDS: R501.1; also elsewhere on the board
unnamed: R501.2, U501.3 (A)
unnamed: U502.6 (LDO33_O), U502.7 (VDD_IO)
UART-CTS: U502.15 (P1_7); also elsewhere on the board
UART-RTS: U502.17 (P0_0); also elsewhere on the board
UART-RX: U502.23 (HCI_TXD); also elsewhere on the board
UART-TX: U502.22 (HCI_RXD); also elsewhere on the board

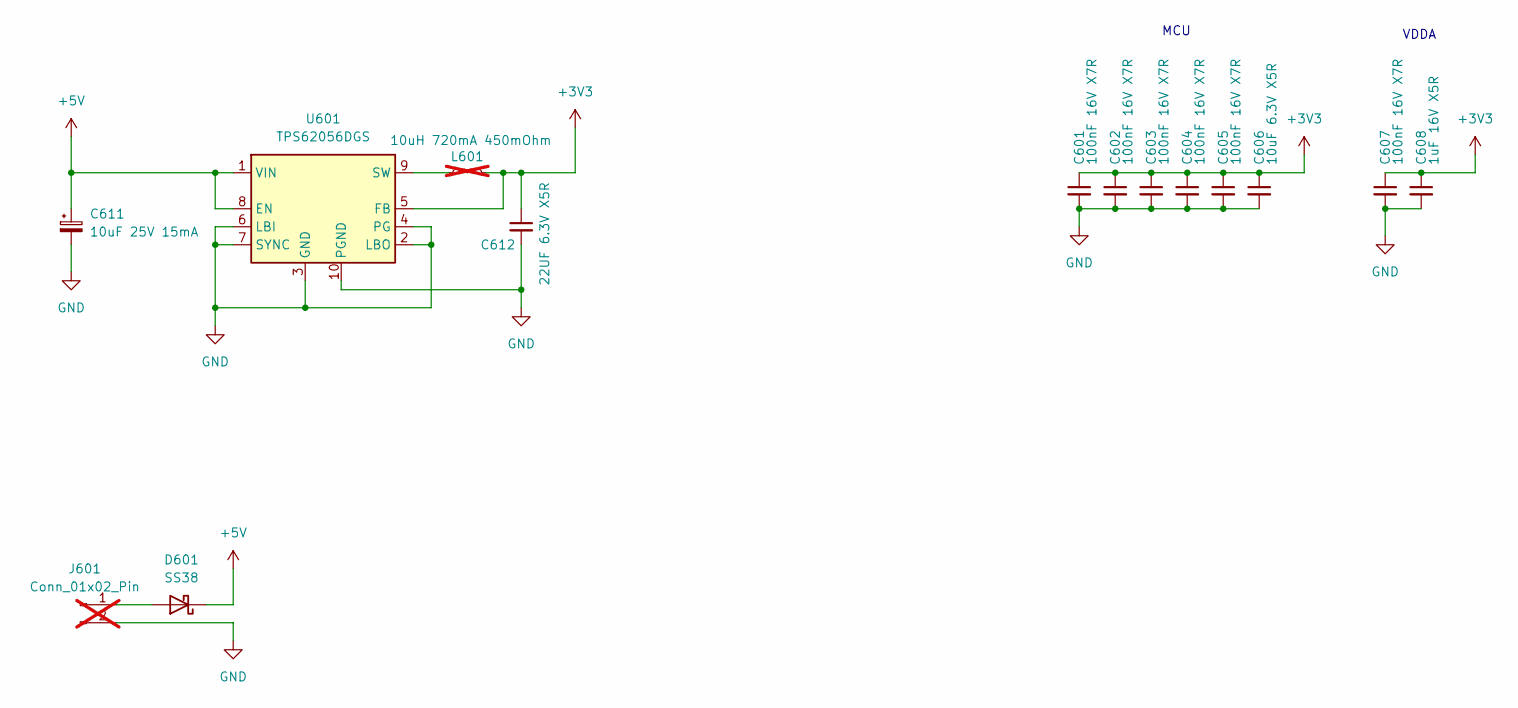
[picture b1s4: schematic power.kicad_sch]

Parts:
C601, C602, C603, C604, C605, C607: 100nF 16V X7R; C_0402_1005Metric; JLCPCB Part # C328914
C606: 10uF 6.3V X5R; C_0402_1005Metric; JLCPCB Part # C15525
C608: 1uF 16V X5R; C_0402_1005Metric; JLCPCB Part # C29266
C611: 10uF 25V 15mA; CP_Elec_4x5.4; JLCPCB Part # C72484
C612: 22UF 6.3V X5R; C_0805_2012Metric; JLCPCB Part # C7467039
D601: SS38; D_SMA; JLCPCB Part # C64999
J601: Conn_01x02_Pin; PinHeader_1x02_P2.54mm_Vertical; JLCPCB Part # Not assembled; not fitted
L601: 10uH 720mA 450mOhm; L_1008_2520Metric; JLCPCB Part # C218827; not fitted
U601: TPS62056DGS; VSSOP-10_3x3mm_P0.5mm; JLCPCB Part # C182547

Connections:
+3V3: C601.1, C602.1, C603.1, C604.1, C605.1, C606.1, C607.1, C608.1, C612.1, L601.2, U601.5 (FB); also elsewhere on the board
+5V: C611.1, D601.1 (K), U601.1 (VIN), U601.8 (EN); also elsewhere on the board
GND: C601.2, C602.2, C603.2, C604.2, C605.2, C606.2, C607.2, C608.2, C611.2, C612.2, J601.2, U601.2 (LBO), U601.3 (GND), U601.4 (PG), U601.6 (LBI), U601.7 (SYNC), U601.10 (PGND); also elsewhere on the board
unnamed: D601.2 (A), J601.1
unnamed: L601.1, U601.9 (SW)

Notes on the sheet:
MCU
VDDA

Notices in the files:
README.md:
License: MIT
Hardware: CERN-OHL-P
hw/christmas-star/christmas-star.kicad_pcb:
© Tuomas Terho
